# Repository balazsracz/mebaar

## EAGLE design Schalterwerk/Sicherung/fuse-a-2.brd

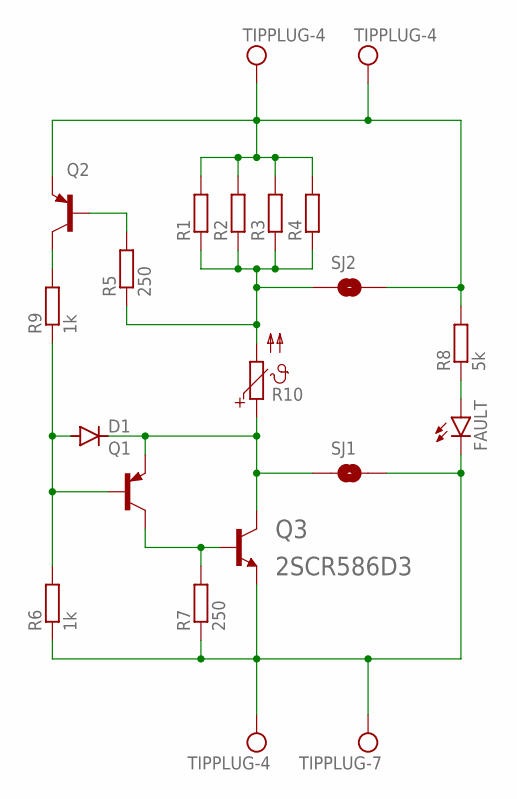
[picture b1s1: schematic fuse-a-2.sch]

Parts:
D1: DIODE-MINIMELF; MINIMELF
FAULT: LEDCHIPLED_0603; CHIPLED_0603
Q1, Q2: BCX71SMD; SOT23
Q3: 2SCR586D3; D-PAK_TO252AA
R1, R2, R3, R4: R-EU_R2512; R2512
R5, R7: 250; R0805
R6, R9: 1k; R0805
R8: 5k; R0805
R10: PTC_1812; PTC1812
SJ1, SJ2: SJRND2; SJ_RND2
U$1, U$2, U$4: TIPPLUG-4; BANANAPLUG-4-LUG
U$3: TIPPLUG-7; BANANAPLUG-7-LUG

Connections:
FUSEIN: R1.1, R2.1, R3.1, R4.1, R5.1, R10.2, SJ2.P$1 (1)
FUSEOUT: D1.C, Q1.2 (E), Q3.4 (C), R10.1, SJ1.P$1 (1)
unnamed: Q2.1 (B), R5.2
unnamed: D1.A, Q1.1 (B), R6.2, R9.1
unnamed: Q1.3 (C), Q3.1 (B), R7.2
unnamed: FAULT.A, R8.1
unnamed: Q2.3 (C), R9.2
VIN: Q2.2 (E), R1.2, R2.2, R3.2, R4.2, R8.2, SJ2.P$2 (2), U$1.4MM, U$4.4MM
VOUT: FAULT.C, Q3.3 (E), R6.1, R7.1, SJ1.P$2 (2), U$2.4MM, U$3.7MM

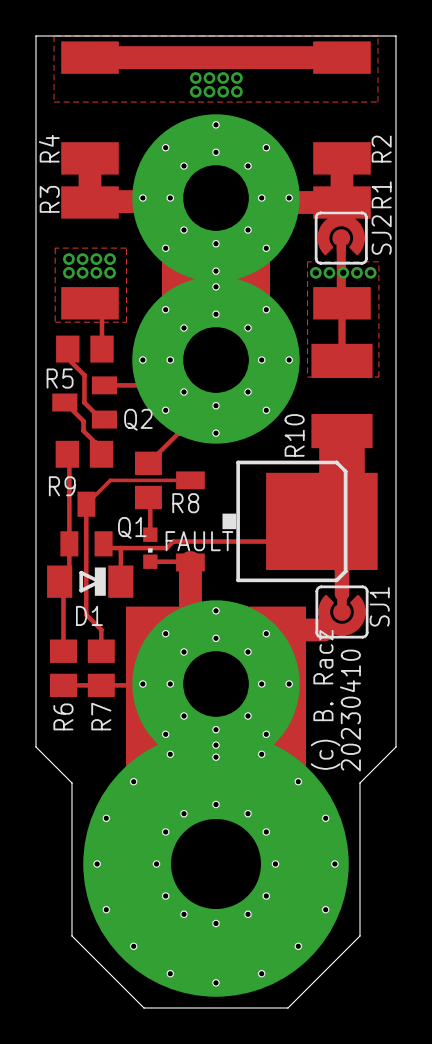
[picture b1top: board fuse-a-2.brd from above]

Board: 2 copper layers, 20.0 x 54.0 mm, 21 parts (0 on the bottom side), 9 nets.

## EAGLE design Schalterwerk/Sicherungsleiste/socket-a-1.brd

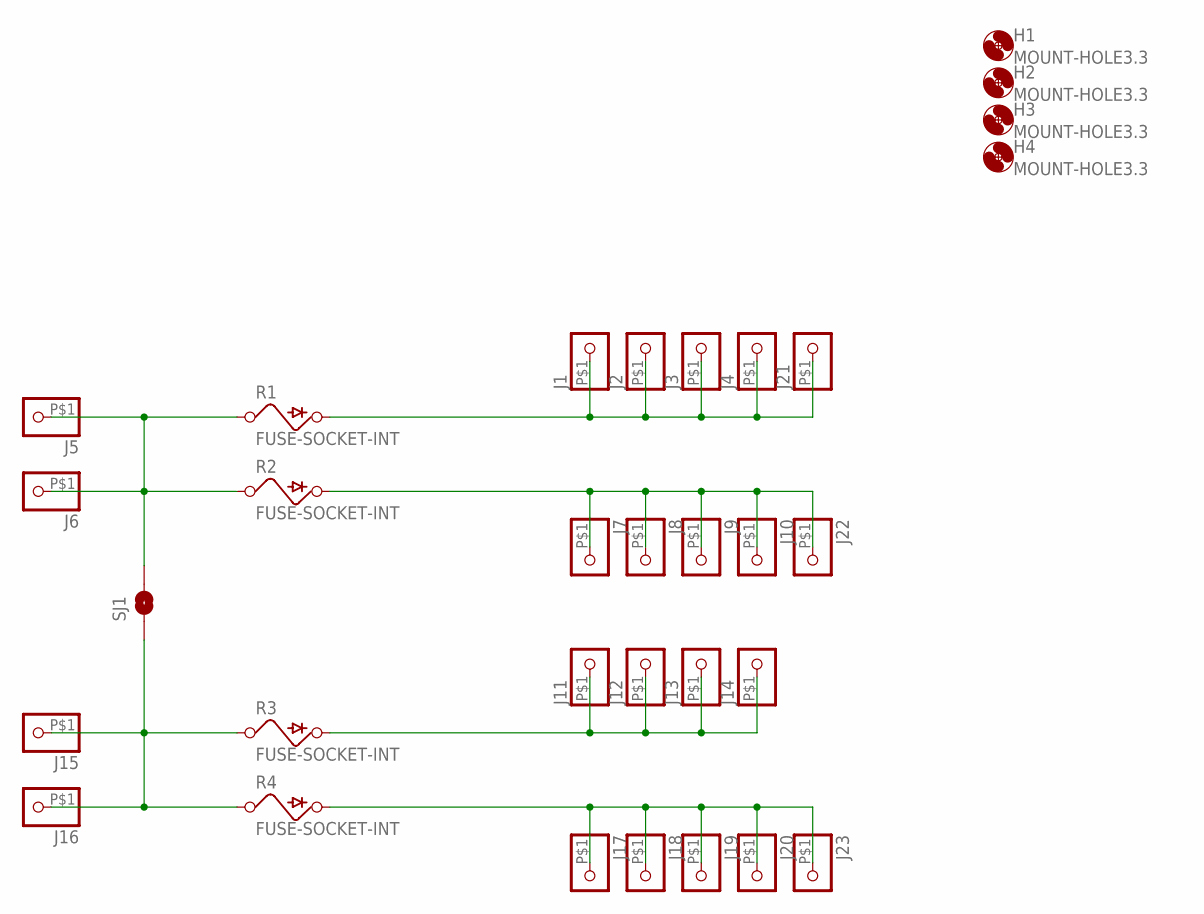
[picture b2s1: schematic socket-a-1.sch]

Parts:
H1, H2, H3, H4: MOUNT-HOLE3.3; 3,3
J1, J2, J3, J4, J5, J6, J7, J8, J9, J10, J11, J12, J13, J14, J15, J16, J17, J18, J19, J20, J21, J22, J23: LARGE-SOLDERPAD
R1, R2, R3, R4: FUSE-SOCKET-INT
SJ1: SJRND2; SJ_RND2

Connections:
unnamed: J15.P$1, J16.P$1, R3.PIN1 (PIN), R3.PIN2 (PIN), R4.PIN1 (PIN), R4.PIN2 (PIN), SJ1.P$1 (1)
unnamed: J11.P$1, J12.P$1, J13.P$1, J14.P$1, R3.POUT
unnamed: J17.P$1, J18.P$1, J19.P$1, J20.P$1, J23.P$1, R4.POUT
unnamed: J5.P$1, J6.P$1, R1.PIN1 (PIN), R1.PIN2 (PIN), R2.PIN1 (PIN), R2.PIN2 (PIN), SJ1.P$2 (2)
unnamed: J1.P$1, J2.P$1, J3.P$1, J4.P$1, J21.P$1, R1.POUT
unnamed: J7.P$1, J8.P$1, J9.P$1, J10.P$1, J22.P$1, R2.POUT

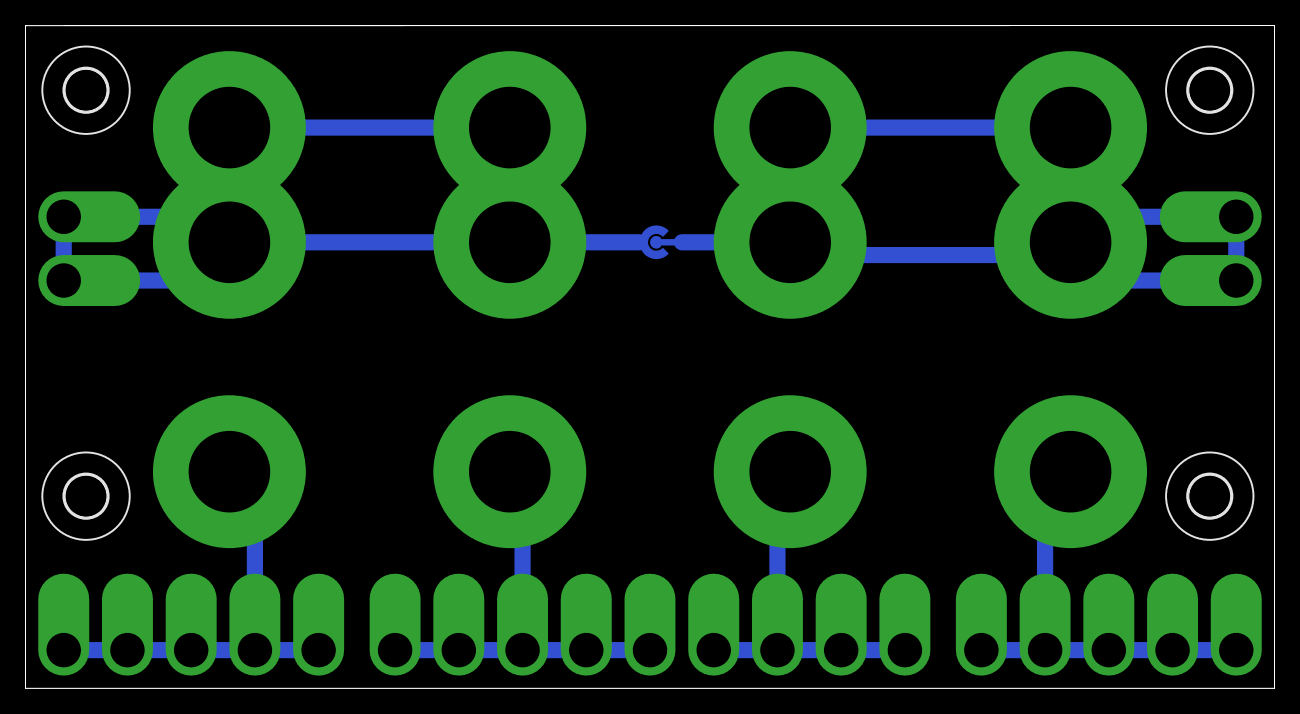
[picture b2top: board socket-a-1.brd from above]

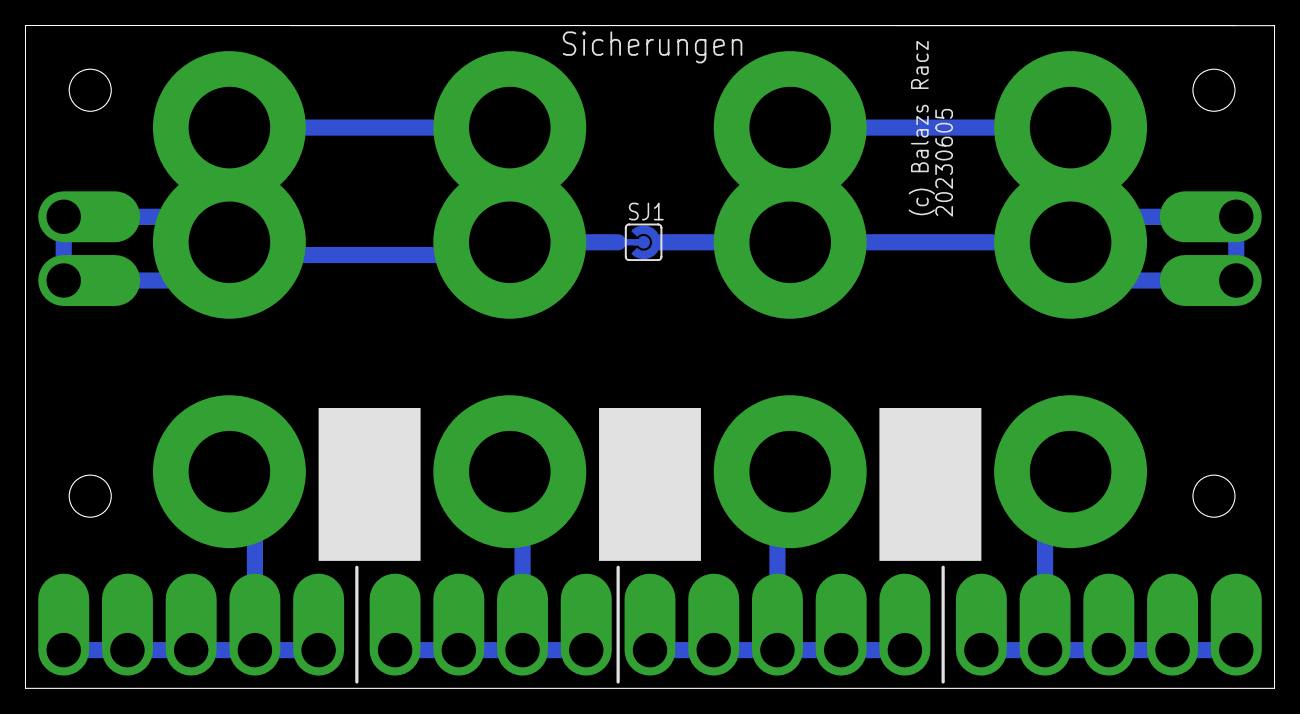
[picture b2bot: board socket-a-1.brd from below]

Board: 2 copper layers, 98.0 x 52.0 mm, 32 parts (28 on the bottom side), 6 nets.

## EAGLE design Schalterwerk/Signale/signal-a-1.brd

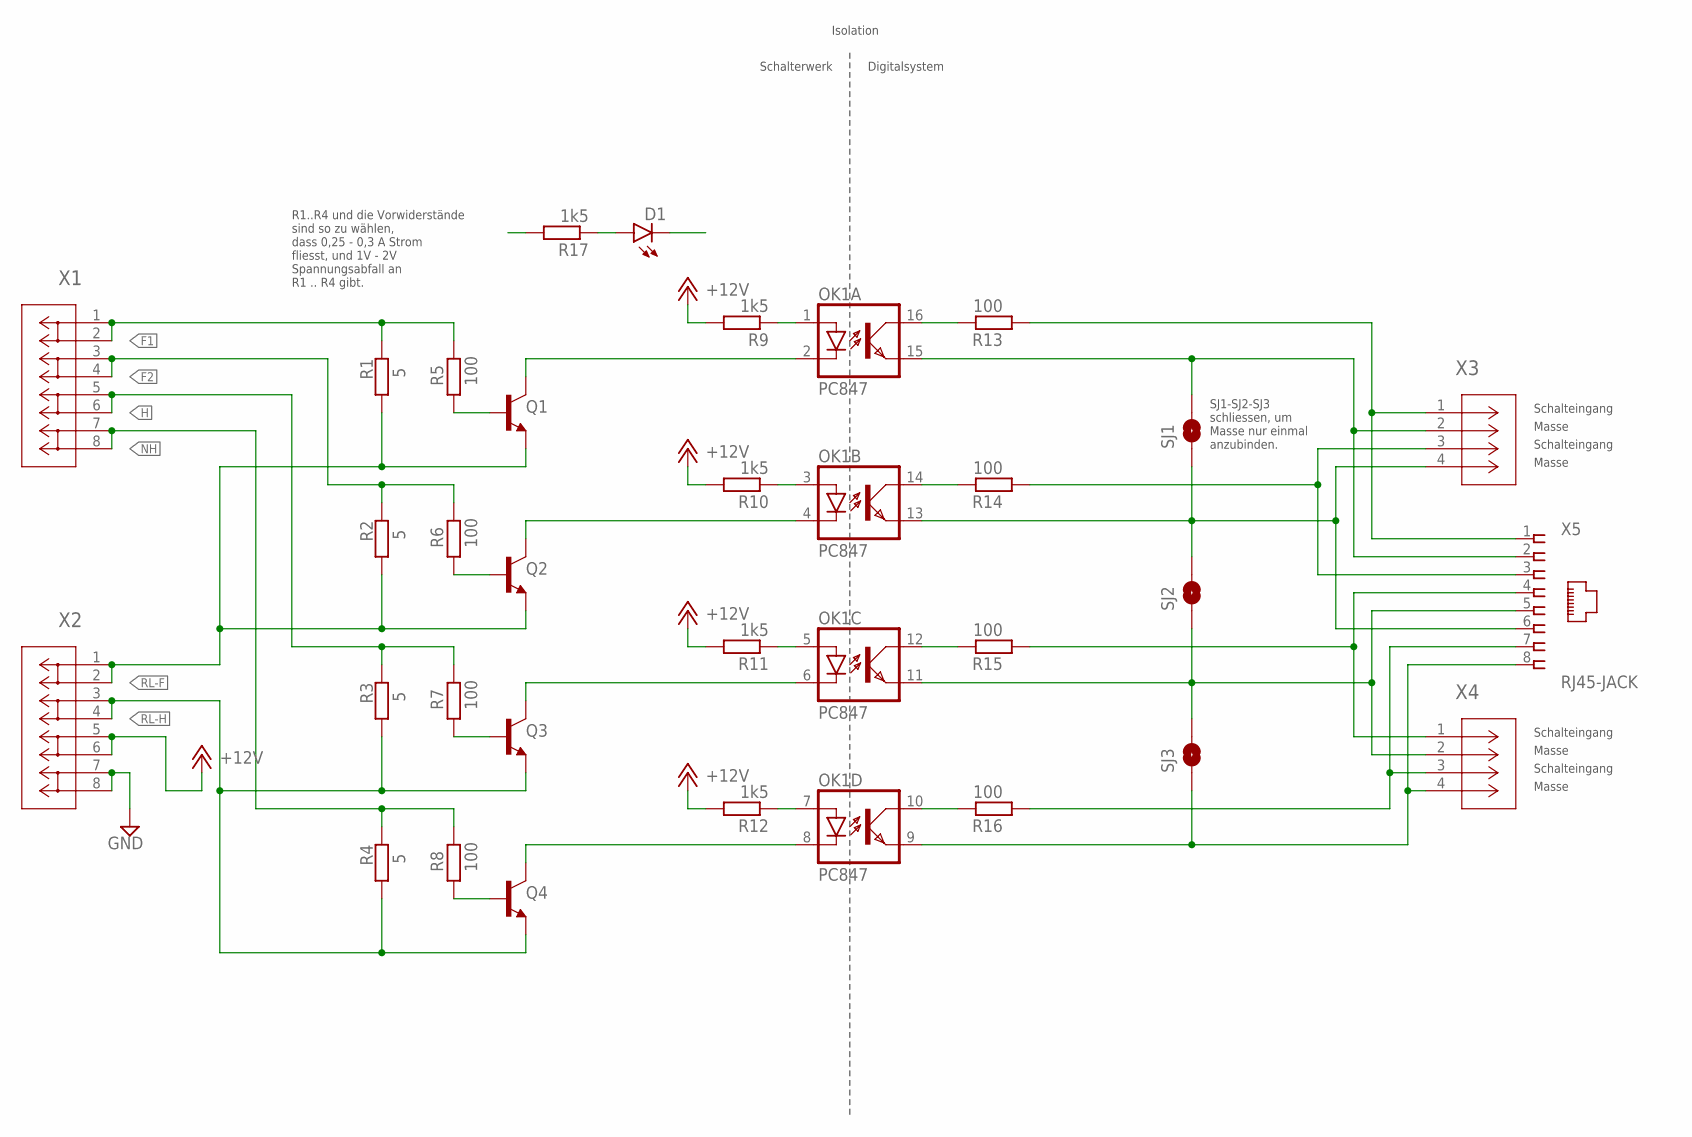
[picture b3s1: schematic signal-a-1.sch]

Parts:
D1: LEDCHIPLED_0603; CHIPLED_0603
OK1: PC847; DIL16
Q1, Q2, Q3, Q4: NPN-23; SOT23
R1, R2, R3, R4: 5; VTA52
R5, R6, R7, R8, R13, R14, R15, R16: 100; R0805
R9, R10, R11, R12, R17: 1k5; R0805
SJ1, SJ2, SJ3: SJRND2; SJ_RND2
X1, X2: PHNX_4P_508CONN_1017493; PHNX_4P_508
X3, X4: PHNX_4P_350CONN_1984989_PXC; PHNX_4P_350
X5: RJ45-JACK; RJ45-PULSE-E5J88

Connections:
+12V: R9.2, R10.2, R11.2, R12.2, X2.5, X2.6
F1: R1.1, R5.2, X1.1, X1.2
F2: R2.1, R6.2, X1.3, X1.4
GND: X2.7, X2.8
GND1: D1.C
H: R3.1, R7.2, X1.5, X1.6
unnamed: Q1.1 (B), R5.1
unnamed: OK1.2 (C), Q1.3 (C)
unnamed: R13.1, X3.1, X5.1
unnamed: OK1.15 (EMIT), SJ1.P$2 (2), X3.2, X5.2
unnamed: OK1.1 (A), R9.1
unnamed: R14.1, X3.3, X5.3
unnamed: Q2.1 (B), R6.1
unnamed: OK1.4 (C), Q2.3 (C)
unnamed: OK1.3 (A), R10.1
unnamed: OK1.5 (A), R11.1
unnamed: OK1.7 (A), R12.1
unnamed: Q3.1 (B), R7.1
unnamed: OK1.6 (C), Q3.3 (C)
unnamed: OK1.11 (EMIT), SJ2.P$1 (1), SJ3.P$2 (2), X4.2, X5.5
unnamed: R16.1, X4.3, X5.7
unnamed: OK1.9 (EMIT), SJ3.P$1 (1), X4.4, X5.8
unnamed: Q4.1 (B), R8.1
unnamed: OK1.8 (C), Q4.3 (C)
unnamed: OK1.16 (COL), R13.2
unnamed: OK1.13 (EMIT), SJ1.P$1 (1), SJ2.P$2 (2), X3.4, X5.6
unnamed: OK1.14 (COL), R14.2
unnamed: OK1.12 (COL), R15.2
unnamed: OK1.10 (COL), R16.2
unnamed: D1.A, R17.1
unnamed: R15.1, X4.1, X5.4
NH: R4.1, R8.2, X1.7, X1.8
RL-F: Q1.2 (E), Q2.2 (E), R1.2, R2.2, X2.1, X2.2
RL-H: Q3.2 (E), Q4.2 (E), R3.2, R4.2, X2.3, X2.4

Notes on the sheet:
Schalteingang
Masse
SJ1-SJ2-SJ3 schliessen, um Masse nur einmal anzubinden.
R1..R4 und die Vorwiderstände sind so zu wählen, dass 0,25 - 0,3 A Strom fliesst, und 1V - 2V Spannungsabfall an R1 .. R4 gibt.
Isolation
Schalterwerk
Digitalsystem

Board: 2 copper layers, 31 parts (0 on the bottom side), 33 nets, no tracks yet.

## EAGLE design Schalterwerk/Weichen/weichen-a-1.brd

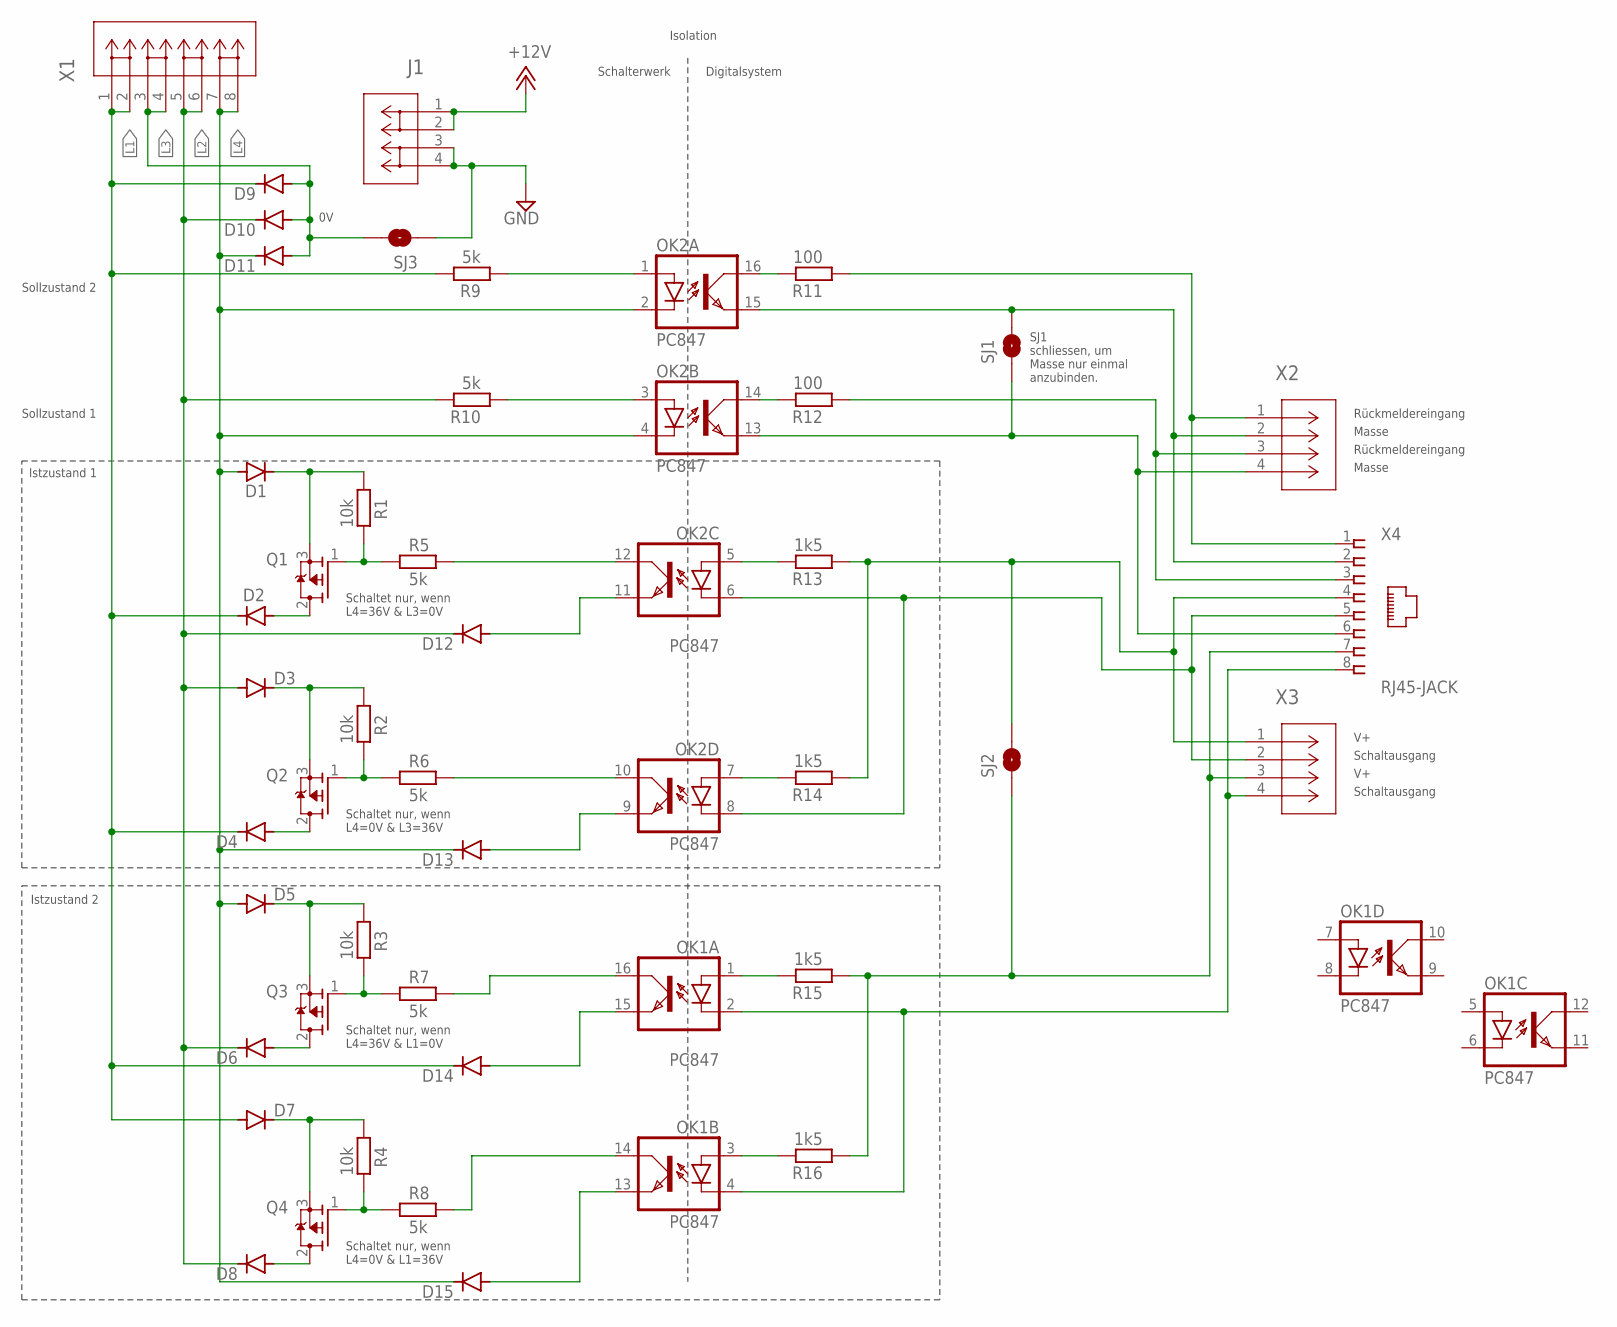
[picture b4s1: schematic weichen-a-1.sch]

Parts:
D1, D2, D3, D4, D5, D6, D7, D8, D9, D10, D11, D12, D13, D14, D15: DIODE-DO214AC; DO214AC
J1: PHNX_2P_508CONN_1017491; PHNX_2P_508
OK1, OK2: PC847; DIL16
Q1, Q2, Q3, Q4: P-MOSFET; DPAK-2
R1, R2, R3, R4: 10k; R0805
R5, R6, R7, R8, R9, R10: 5k; R0805
R11, R12: 100; R0805
R13, R14, R15, R16: 1k5; R0805
SJ1, SJ2, SJ3: SJRND2; SJ_RND2
X1: PHNX_4P_508CONN_1017493; PHNX_4P_508
X2, X3: PHNX_4P_350CONN_1984989_PXC; PHNX_4P_350
X4: RJ45-JACK; RJ45-PULSE-E5J88

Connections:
+12V: J1.1, J1.2
GND: J1.3, J1.4, SJ3.P$1 (1)
L1: D2.C, D4.C, D7.A, D9.C, D14.C, R9.2, X1.1, X1.2
L2: D3.A, D6.C, D8.C, D10.C, D12.C, R10.2, X1.5, X1.6
L3: D9.A, D10.A, D11.A, SJ3.P$2 (2), X1.3, X1.4
L4: D1.A, D5.A, D11.C, D13.C, D15.C, OK2.2 (C), OK2.4 (C), X1.7, X1.8
unnamed: D3.C, Q2.3 (S), R2.1
unnamed: OK2.1 (A), R9.1
unnamed: R11.1, X2.1, X4.1
unnamed: OK2.15 (EMIT), SJ1.P$2 (2), X2.2, X4.2
unnamed: OK2.5 (A), R13.2
unnamed: R12.1, X2.3, X4.3
unnamed: OK2.3 (A), R10.1
unnamed: OK2.7 (A), R14.2
unnamed: Q1.1 (G), R1.2, R5.1
unnamed: OK2.12 (COL), R5.2
unnamed: OK2.10 (COL), R6.2
unnamed: Q2.1 (G), R2.2, R6.1
unnamed: D1.C, Q1.3 (S), R1.1
unnamed: OK2.6 (C), OK2.8 (C), X3.2, X4.5
unnamed: R15.1, R16.1, SJ2.P$1 (1), X3.3, X4.7
unnamed: OK1.2 (C), OK1.4 (C), X3.4, X4.8
unnamed: D12.A, OK2.11 (EMIT)
unnamed: D2.A, Q1.2 (D)
unnamed: OK2.16 (COL), R11.2
unnamed: OK2.13 (EMIT), SJ1.P$1 (1), X2.4, X4.6
unnamed: OK2.14 (COL), R12.2
unnamed: D13.A, OK2.9 (EMIT)
unnamed: D4.A, Q2.2 (D)
unnamed: OK1.1 (A), R15.2
unnamed: OK1.3 (A), R16.2
unnamed: R13.1, R14.1, SJ2.P$2 (2), X3.1, X4.4
unnamed: OK1.16 (COL), R7.2
unnamed: Q3.1 (G), R3.2, R7.1
unnamed: OK1.14 (COL), R8.2
unnamed: Q4.1 (G), R4.2, R8.1
unnamed: D7.C, Q4.3 (S), R4.1
unnamed: D5.C, Q3.3 (S), R3.1
unnamed: D14.A, OK1.15 (EMIT)
unnamed: D6.A, Q3.2 (D)
unnamed: D15.A, OK1.13 (EMIT)
unnamed: D8.A, Q4.2 (D)

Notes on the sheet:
Rückmeldereingang
Masse
Schaltausgang
SJ1 schliessen, um Masse nur einmal anzubinden.
Isolation
Schalterwerk
Digitalsystem
Schaltet nur, wenn L4=36V & L3=0V
Schaltet nur, wenn L4=0V & L3=36V
Schaltet nur, wenn L4=36V & L1=0V
Schaltet nur, wenn L4=0V & L1=36V
Sollzustand 2
Sollzustand 1
Istzustand 1
Istzustand 2

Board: 2 copper layers, 45 parts (0 on the bottom side), 42 nets, no tracks yet.

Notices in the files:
Schalterwerk/Sicherungsleiste/socket-a-1.sch:
LICENSE: Licensed by the Solderpad Hardware License V2.0
parts and their libraries:
COPYRIGHT: Copyright (C) 2023 Ultra Librarian. All rights reserved.
